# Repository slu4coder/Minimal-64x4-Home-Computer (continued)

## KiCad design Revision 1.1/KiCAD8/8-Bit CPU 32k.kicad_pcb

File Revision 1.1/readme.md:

# Revision 1.1 (Original Release)

The folder 'KiCAD' contains KiCAD 6 schematics. The folder 'KiCAD8' contains the same schematics with minor cosmetic updates, converted to KiCAD8.
For the bill of materials (BOM) please refer to chapter 'Hardware' of the 'Minimal 64x4 Reference Manual'. Follow the link in the root readme.md of this repo.

The folder 'Support' contains the cross-platform assembler und the emulator (Win).
The folder 'Programs' contains native Minimal 64x4 code.

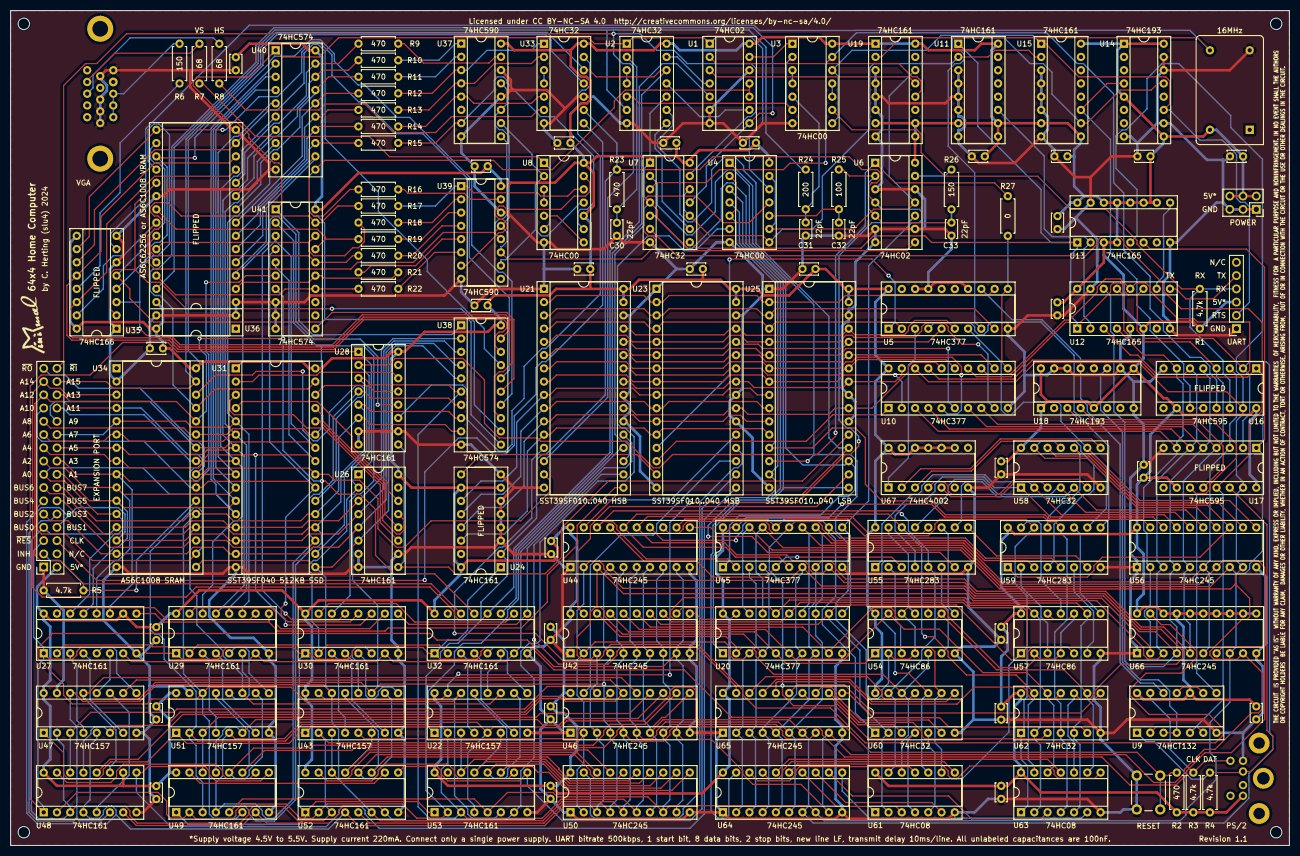
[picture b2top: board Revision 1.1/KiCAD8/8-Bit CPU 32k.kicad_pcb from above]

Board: 2 copper layers, 245.1 x 160.0 mm, 138 parts (0 on the bottom side), 267 nets.

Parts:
C1, C2, C3, C4, C5, C6, C7, C8, C9, C10, C11, C12, C13, C14, C15, C16, C17, C18, C19, C20, C21, C22, C23, C24, C25, C26, C27, C28, C29: 100nF; C_Disc_D3.4mm_W2.1mm_P2.50mm
C30, C31, C32, C33: 22pF; C_Disc_D3.4mm_W2.1mm_P2.50mm
H1, H2, H3, H4: M2; MountingHole_2.2mm_M2
J1: UART; PinSocket_1x06_P2.54mm_Vertical
J2: PS/2; FP_MINI_DIN_6_PS2
J3: EXPANSION PORT; PinSocket_2x16_P2.54mm_Vertical
J4: VGA; VGA DSUB15HD_female
J5: POWER; PinSocket_2x03_P2.54mm_Vertical
R1, R3, R4, R5: 4.7k; R_Axial_DIN0207_L6.3mm_D2.5mm_P7.62mm_Horizontal
R2, R9, R10, R11, R12, R13, R14, R15, R16, R17, R18, R19, R20, R21, R22, R23: 470; R_Axial_DIN0207_L6.3mm_D2.5mm_P7.62mm_Horizontal
R6, R26: 150; R_Axial_DIN0207_L6.3mm_D2.5mm_P7.62mm_Horizontal
R7, R8: 68; R_Axial_DIN0207_L6.3mm_D2.5mm_P7.62mm_Horizontal
R24: 200; R_Axial_DIN0207_L6.3mm_D2.5mm_P7.62mm_Horizontal
R25: 100; R_Axial_DIN0207_L6.3mm_D2.5mm_P7.62mm_Horizontal
R27: 0; R_Axial_DIN0207_L6.3mm_D2.5mm_P7.62mm_Horizontal
SW1: RESET; SW_PUSH_6mm
U1, U6: 74HC02; DIP-14_W7.62mm_Socket
U2, U7, U33, U58, U60, U62: 74HC32; DIP-14_W7.62mm_Socket
U3, U4, U8: 74HC00; DIP-14_W7.62mm_Socket
U5, U10, U20, U45: 74HC377; DIP-20_W7.62mm_Socket
U9: 74HCT132; DIP-14_W7.62mm_Socket
U11, U15, U19, U24, U26, U27, U28, U29, U30, U32, U48, U49, U52, U53: 74HC161; DIP-16_W7.62mm_Socket
U12, U13: 74HC165; DIP-16_W7.62mm_Socket
U14, U18: 74HC193; DIP-16_W7.62mm_Socket
U16, U17: 74HC595; DIP-16_W7.62mm_Socket
U21: SST39SF010..040 HSB; DIP-32_W15.24mm_Socket
U22, U43, U47, U51: 74HC157; DIP-16_W7.62mm_Socket
U23: SST39SF010..040 MSB; DIP-32_W15.24mm_Socket
U25: SST39SF010..040 LSB; DIP-32_W15.24mm_Socket
U31: SST39SF040 512KB SSD; DIP-32_W15.24mm_Socket
U34: AS6C1008 SRAM; DIP-32_W15.24mm_Socket
U35: 74HC166; DIP-16_W7.62mm_Socket
U36: AS6C62256 or AS6C1008 VRAM; DIP-32_W15.24mm_Socket
U37, U39: 74HC590; DIP-16_W7.62mm_Socket
U38, U40, U41: 74HC574; DIP-20_W7.62mm_Socket
U42, U44, U46, U50, U56, U64, U65, U66: 74HC245; DIP-20_W7.62mm_Socket
U54, U57: 74HC86; DIP-14_W7.62mm_Socket
U55, U59: 74HC283; DIP-16_W7.62mm_Socket
U61, U63: 74HC08; DIP-14_W7.62mm_Socket
U67: 74HC4002; DIP-14_W7.62mm_Socket
X1: 16MHz; Oscillator_DIP-14

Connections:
16MHz: U19.2 (CP), U35.7 (CP), X1.8 (OUT)
+5V: C1.1, C2.1, C3.1, C4.1, C5.1, C6.1, C7.1, C8.1, C9.1, C10.1, C11.1, C12.1, C13.1, C14.1, C15.1, C16.1, C17.1, C18.1, C19.1, C20.1, C21.1, C22.1, C23.1, C24.1, C25.1, C26.1, C27.1, C28.1, C29.1, J1.3, J2.4, J3.2, J5.2, J5.4, J5.6, R1.1, R2.1, R3.1, R4.1, U1.14 (VCC), U2.14 (VCC), U3.14 (VCC), U4.14 (VCC), U5.20 (VCC), U6.14 (VCC), U7.14 (VCC), U8.10, U8.14 (VCC), U9.10, U9.14 (VCC), U10.20 (VCC), U11.7 (CEP), U11.9 (~PE), U11.10 (CET), U11.16 (VCC), U12.6 (D7), U12.16 (VCC), U13.3 (D4), U13.4 (D5), U13.10 (DS), U13.11 (D0), U13.12 (D1), U13.13 (D2), U13.14 (D3), U13.16 (VCC), U14.1 (D1), U14.5 (CPU), U14.9 (D3), U14.16 (VCC), U15.7 (CEP), U15.9 (~PE), U15.16 (VCC), U16.10 (~SRCLR), U16.16 (VCC), U17.10 (~SRCLR), U17.16 (VCC), U18.1 (D1), U18.5 (CPU), U18.9 (D3), U18.16 (VCC), U19.1 (~MR), U19.7 (CEP), U19.9 (~PE), U19.10 (CET), U19.16 (VCC), U20.20 (VCC), U21.31 (~WE), U21.32 (VCC), U22.16 (VCC), U23.31 (~WE), U23.32 (VCC), U24.7 (CEP), U24.10 (CET), U24.16 (VCC), U25.31 (~WE), U25.32 (VCC), U26.16 (VCC), U27.10 (CET), U27.16 (VCC), U28.16 (VCC), U29.16 (VCC), U30.16 (VCC), U31.32 (VCC), U32.16 (VCC), U33.14 (VCC), U34.32 (VCC), U35.9 (MR), U35.16 (VCC), U36.30 (CE2), U36.32 (VCC), U37.16 (VCC), U38.20 (VCC), U39.16 (VCC), U40.20 (VCC), U41.20 (VCC), U42.20 (VCC), U43.16 (VCC), U44.20 (VCC), U45.20 (VCC), U46.20 (VCC), U47.16 (VCC), U48.10 (CET), U48.16 (VCC), U49.16 (VCC), U50.20 (VCC), U51.16 (VCC), U52.16 (VCC), U53.16 (VCC), U54.14 (VCC), U55.16 (VCC), U56.20 (VCC), U57.14 (VCC), U58.14 (VCC), U59.16 (VCC), U60.14 (VCC), U61.14 (VCC), U62.14 (VCC), U63.14 (VCC), U64.20 (VCC), U65.20 (VCC), U66.11 (B7), U66.12 (B6), U66.13 (B5), U66.14 (B4), U66.15 (B3), U66.16 (B2), U66.17 (B1), U66.18 (B0), U66.20 (VCC), U67.9, U67.10, U67.11, U67.12, U67.14 (VDD), X1.14 (Vcc)
/ALU/A0: U44.18 (B0), U45.2 (Q0), U55.5 (A1), U60.13, U61.13
/ALU/A1: U44.17 (B1), U45.5 (Q1), U55.3 (A2), U60.10, U61.10
/ALU/A2: U44.16 (B2), U45.6 (Q2), U55.14 (A3), U62.13, U63.13
/ALU/A3: U44.15 (B3), U45.9 (Q3), U55.12 (A4), U62.10, U63.10
/ALU/A4: U44.14 (B4), U45.12 (Q4), U59.5 (A1), U60.1, U61.1
/ALU/A5: U44.13 (B5), U45.15 (Q5), U59.3 (A2), U60.4, U61.4
/ALU/A6: U44.12 (B6), U45.16 (Q6), U59.14 (A3), U62.1, U63.1
/ALU/A7: U44.11 (B7), U45.19 (Q7), U59.12 (A4), U62.4, U63.4
/ALU/B0: U20.2 (Q0), U42.18 (B0), U54.5, U60.12, U61.12
/ALU/B1: U20.5 (Q1), U42.17 (B1), U54.1, U60.9, U61.9
/ALU/B2: U20.6 (Q2), U42.16 (B2), U54.13, U62.12, U63.12
/ALU/B3: U20.9 (Q3), U42.15 (B3), U54.9, U62.9, U63.9
/ALU/B4: U20.12 (Q4), U42.14 (B4), U57.5, U60.2, U61.2
/ALU/B5: U20.15 (Q5), U42.13 (B5), U57.1, U60.5, U61.5
/ALU/B6: U20.16 (Q6), U42.12 (B6), U57.13, U62.2, U63.2
/ALU/B7: U20.19 (Q7), U42.11 (B7), U57.9, U62.5, U63.5
/ALU/BUS0: J3.7, U10.3 (D0), U12.4 (D5), U16.7 (QH), U17.7 (QH), U20.3 (D0), U26.3 (D0), U31.13 (I/O0), U34.13 (I/O0), U38.2 (D0), U42.2 (A0), U43.2 (I0a), U44.2 (A0), U45.3 (D0), U46.2 (A0), U47.2 (I0a), U48.3 (D0), U50.2 (A0), U52.3 (D0), U56.2 (A0), U64.2 (A0), U65.2 (A0), U66.2 (A0)
/ALU/BUS1: J3.8, U10.4 (D1), U12.3 (D4), U16.6 (QG), U17.6 (QG), U20.4 (D1), U26.4 (D1), U31.14 (I/O1), U34.14 (I/O1), U38.3 (D1), U42.3 (A1), U43.5 (I0b), U44.3 (A1), U45.4 (D1), U46.3 (A1), U47.5 (I0b), U48.4 (D1), U50.3 (A1), U52.4 (D1), U56.3 (A1), U64.3 (A1), U65.3 (A1), U66.3 (A1)
/ALU/BUS2: J3.9, U10.7 (D2), U12.14 (D3), U16.5 (QF), U17.5 (QF), U20.7 (D2), U26.5 (D2), U31.15 (I/O2), U34.15 (I/O2), U38.4 (D2), U42.4 (A2), U43.11 (I0c), U44.4 (A2), U45.7 (D2), U46.4 (A2), U47.11 (I0c), U48.5 (D2), U50.4 (A2), U52.5 (D2), U56.4 (A2), U64.4 (A2), U65.4 (A2), U66.4 (A2)
/ALU/BUS3: J3.10, U10.8 (D3), U12.13 (D2), U16.4 (QE), U17.4 (QE), U20.8 (D3), U26.6 (D3), U31.17 (I/O3), U34.17 (I/O3), U38.5 (D3), U42.5 (A3), U43.14 (I0d), U44.5 (A3), U45.8 (D3), U46.5 (A3), U47.14 (I0d), U48.6 (D3), U50.5 (A3), U52.6 (D3), U56.5 (A3), U64.5 (A3), U65.5 (A3), U66.5 (A3)
/ALU/BUS4: J3.11, U10.13 (D4), U12.12 (D1), U16.3 (QD), U17.3 (QD), U20.13 (D4), U22.2 (I0a), U28.3 (D0), U31.18 (I/O4), U34.18 (I/O4), U38.6 (D4), U42.6 (A4), U44.6 (A4), U45.13 (D4), U46.6 (A4), U49.3 (D0), U50.6 (A4), U51.2 (I0a), U53.3 (D0), U56.6 (A4), U64.6 (A4), U65.6 (A4), U66.6 (A4)
/ALU/BUS5: J3.12, U10.14 (D5), U12.11 (D0), U16.2 (QC), U17.2 (QC), U20.14 (D5), U22.5 (I0b), U28.4 (D1), U31.19 (I/O5), U34.19 (I/O5), U38.7 (D5), U42.7 (A5), U44.7 (A5), U45.14 (D5), U46.7 (A5), U49.4 (D1), U50.7 (A5), U51.5 (I0b), U53.4 (D1), U56.7 (A5), U64.7 (A5), U65.7 (A5), U66.7 (A5)
/ALU/BUS6: J3.13, U10.17 (D6), U13.6 (D7), U16.1 (QB), U17.1 (QB), U20.17 (D6), U22.11 (I0c), U28.5 (D2), U31.20 (I/O6), U34.20 (I/O6), U38.8 (D6), U42.8 (A6), U44.8 (A6), U45.17 (D6), U46.8 (A6), U49.5 (D2), U50.8 (A6), U51.11 (I0c), U53.5 (D2), U56.8 (A6), U64.8 (A6), U65.8 (A6), U66.8 (A6)
/ALU/BUS7: J3.14, U10.18 (D7), U13.5 (D6), U16.15 (QA), U17.15 (QA), U20.18 (D7), U22.14 (I0d), U28.6 (D3), U31.21 (I/O7), U34.21 (I/O7), U38.9 (D7), U42.9 (A7), U44.9 (A7), U45.18 (D7), U46.9 (A7), U49.6 (D3), U50.9 (A7), U51.14 (I0d), U53.6 (D3), U56.9 (A7), U64.9 (A7), U65.9 (A7), U66.9 (A7)
/ALU/C_FLG: U5.4 (D1), U59.9 (C4)
/ALU/EC: U4.4, U25.15 (I/O2), U55.7 (C0)
/ALU/ES: U4.1, U25.14 (I/O1), U54.2, U54.4, U54.10, U54.12, U57.2, U57.4, U57.10, U57.12
/ALU/N_FLG: U5.7 (D2), U56.11 (B7), U58.9, U59.10 (S4)
/ALU/Z_FLG: U5.3 (D0), U67.1
/ALU/~AND: U4.3, U64.19 (CE)
/ALU/~EO: U4.2, U4.5, U25.13 (I/O0), U56.19 (CE)
/ALU/~OR: U4.6, U65.19 (CE)
/Control Logic/2MHz: U1.2, U19.12 (Q2)
/Control Logic/4MHz: U1.3, U19.13 (Q1)
/Control Logic/8MHz: U4.9, U4.13, U6.11, U19.14 (Q0)
/Control Logic/CE: U23.21 (I/O7), U48.7 (CEP), U49.7 (CEP), U52.7 (CEP), U53.7 (CEP)
/Control Logic/Flag0: U5.2 (Q0), U21.4 (A12), U23.4 (A12), U25.4 (A12)
/Control Logic/Flag1: U5.5 (Q1), U21.28 (A13), U23.28 (A13), U25.28 (A13)
/Control Logic/Flag2: U5.6 (Q2), U21.29 (A14), U23.29 (A14), U25.29 (A14)
/Control Logic/Flag3: U5.9 (Q3), U21.3 (A15), U23.3 (A15), U25.3 (A15)
/Control Logic/Flag4: U5.12 (Q4), U21.2 (A16), U23.2 (A16), U25.2 (A16)
/Control Logic/Inst0: U10.2 (Q0), U21.8 (A4), U23.8 (A4), U25.8 (A4)
/Control Logic/Inst1: U10.5 (Q1), U21.7 (A5), U23.7 (A5), U25.7 (A5)
/Control Logic/Inst2: U10.6 (Q2), U21.6 (A6), U23.6 (A6), U25.6 (A6)
/Control Logic/Inst3: U10.9 (Q3), U21.5 (A7), U23.5 (A7), U25.5 (A7)
/Control Logic/Inst4: U10.12 (Q4), U21.27 (A8), U23.27 (A8), U25.27 (A8)
/Control Logic/Inst5: U10.15 (Q5), U21.26 (A9), U23.26 (A9), U25.26 (A9)
/Control Logic/Inst6: U10.16 (Q6), U21.23 (A10), U23.23 (A10), U25.23 (A10)
/Control Logic/Inst7: U10.19 (Q7), U21.25 (A11), U23.25 (A11), U25.25 (A11)
/Control Logic/MC: U21.20 (I/O6), U22.1 (S), U43.1 (S), U47.1 (S), U51.1 (S)
/Control Logic/ME: U21.21 (I/O7), U27.7 (CEP), U29.7 (CEP), U30.7 (CEP), U32.7 (CEP)
/Control Logic/MZ: U6.10, U22.15 (E), U43.15 (E)
/Control Logic/Step0: U21.12 (A0), U23.12 (A0), U24.14 (Q0), U25.12 (A0)
/Control Logic/Step1: U21.11 (A1), U23.11 (A1), U24.13 (Q1), U25.11 (A1)
/Control Logic/Step2: U21.10 (A2), U23.10 (A2), U24.12 (Q2), U25.10 (A2)
/Control Logic/Step3: U21.9 (A3), U23.9 (A3), U24.11 (Q3), U25.9 (A3)
/Control Logic/VREG_CP: U1.10, U1.11, U38.11 (Cp), U40.11 (Cp), U41.11 (Cp)
/Control Logic/~AI: U7.2, U25.19 (I/O5), U45.1 (EN)
/Control Logic/~AO: U2.9, U25.20 (I/O6), U44.19 (CE)
/Control Logic/~BI: U7.5, U20.1 (EN), U25.17 (I/O3)
/Control Logic/~BO: U25.18 (I/O4), U42.19 (CE)
/Control Logic/~CIH: U23.18 (I/O4), U52.9 (~PE), U53.9 (~PE)
/Control Logic/~CIL: U23.17 (I/O3), U48.9 (~PE), U49.9 (~PE)
/Control Logic/~COH: U23.20 (I/O6), U50.19 (CE)
/Control Logic/~COL: U23.19 (I/O5), U46.19 (CE)
/Control Logic/~FF: U21.13 (I/O0), U66.19 (CE)
/Control Logic/~FI: U5.1 (EN), U23.13 (I/O0)
/Control Logic/~IC: U23.15 (I/O2), U24.9 (~PE)
/Control Logic/~II: U10.1 (EN), U23.14 (I/O1)
/Control Logic/~KO: U7.6, U9.5, U17.13 (~OE)
/Control Logic/~MIH: U21.18 (I/O4), U30.9 (~PE), U32.9 (~PE)
/Control Logic/~MIL: U21.17 (I/O3), U27.9 (~PE), U29.9 (~PE)
/Control Logic/~MZ: U2.10, U6.8, U7.1, U7.4, U21.19 (I/O5)
/Control Logic/~NI: U25.21 (I/O7), U26.9 (~PE), U28.9 (~PE)
/Control Logic/~PS2_DR: U5.13 (D4), U9.12, U18.13 (~TCD)
/Control Logic/~RI_PLS: U1.8, U7.11, U31.31 (~WE), U34.29 (~WE)
/Control Logic/~RI: J3.32, U7.13, U21.14 (I/O1)
/Control Logic/~RO: J3.31, U21.15 (I/O2), U31.24 (~OE), U34.24 (~OE)
/Control Logic/~TI_PLS: U7.8, U11.1 (~MR), U12.1 (~PL), U13.1 (~PL)
/Control Logic/~TO: U3.13, U7.3, U16.13 (~OE)
/Control Logic/~UART_DR: U5.8 (D3), U14.13 (~TCD), U15.10 (CET)
/Control Logic/~VREG_OE: U1.1, U2.1, U4.12, U38.1 (OE), U40.1 (OE), U41.1 (OE)
/Control Logic/~V_NEXT: U4.11, U35.15 (PE), U36.24 (~OE), U37.11 (CPC), U37.13 (CPR), U39.11 (CPC), U39.13 (CPR)
/Control Logic/~V_RI_PLS: R24.1, U2.6, U36.29 (~WE)
/Memory and MAR/BANK0: U26.14 (Q0), U31.4 (A12)
/Memory and MAR/BANK1: U26.13 (Q1), U31.28 (A13)
/Memory and MAR/BANK2: U26.12 (Q2), U31.29 (A14)
/Memory and MAR/BANK3: U26.11 (Q3), U31.3 (A15)
/Memory and MAR/BANK4: U28.14 (Q0), U31.2 (A16)
/Memory and MAR/BANK5: U28.13 (Q1), U31.30 (A17)
/Memory and MAR/BANK6: U28.12 (Q2), U31.1 (A18)
/Memory and MAR/BANK7: U28.11 (Q3), U33.13
/Memory and MAR/INH: J3.3, R5.2, U34.22 (~CE)
/PS2 Receiver/PS2_CLK: J2.5, R3.2, U9.13
/PS2 Receiver/PS2_DAT: J2.1, R4.2, U9.1, U17.14 (SER)
/UART/UART_RTS: J1.2, U3.8, U3.12, U14.11 (~PL), U15.1 (~MR)
/UART/UART_RX: J1.4, R1.2, U3.9, U16.14 (SER)
/UART/UART_TX: J1.5, U12.9 (Q7)
/VGA/B0: U35.14 (D7), U36.13 (I/O0), U38.19 (Q0)
/VGA/B1: U35.12 (D6), U36.14 (I/O1), U38.18 (Q1)
/VGA/B2: U35.11 (D5), U36.15 (I/O2), U38.17 (Q2)
/VGA/B3: U35.10 (D4), U36.17 (I/O3), U38.16 (Q3)
/VGA/B4: U35.5 (D3), U36.18 (I/O4), U38.15 (Q4)
/VGA/B5: U35.4 (D2), U36.19 (I/O5), U38.14 (Q5)
/VGA/B6: U35.3 (D1), U36.20 (I/O6), U38.13 (Q6)
/VGA/B7: U35.2 (D0), U36.21 (I/O7), U38.12 (Q7)
/VGA/H1: R9.2, U37.15 (Q0)
/VGA/H2: R10.2, U37.1 (Q1)
/VGA/H4: R11.2, U37.2 (Q2)
/VGA/H8: R12.2, U33.1, U37.3 (Q3)
/VGA/H16: R13.2, U33.2, U37.4 (Q4)
/VGA/H32: R14.2, U33.5, U37.5 (Q5)
/VGA/V1: R15.2, U8.9, U37.7 (Q7)
/VGA/V2: R16.2, U39.15 (Q0)
/VGA/V4: R17.1, U8.12, U39.1 (Q1)
/VGA/V8: R18.1, U39.2 (Q2)
/VGA/V16: R19.1, U39.3 (Q3)
/VGA/V32: R20.1, U39.4 (Q4)
/VGA/V64: R21.2, U39.5 (Q5)
/VGA/V128: R22.1, U39.6 (Q6)
/VGA/V256: U8.13, U39.7 (Q7)
/VGA/V_A0: R9.1, U36.12 (A0), U40.19 (Q0)
/VGA/V_A1: R10.1, U36.11 (A1), U40.18 (Q1)
/VGA/V_A2: R11.1, U36.10 (A2), U40.17 (Q2)
/VGA/V_A3: R12.1, U36.9 (A3), U40.16 (Q3)
/VGA/V_A4: R13.1, U36.8 (A4), U40.15 (Q4)
/VGA/V_A5: R14.1, U36.7 (A5), U40.14 (Q5)
/VGA/V_A6: R15.1, U36.6 (A6), U40.13 (Q6)
/VGA/V_A7: R16.1, U36.5 (A7), U40.12 (Q7)
/VGA/V_A8: R17.2, U36.27 (A8), U41.19 (Q0)
/VGA/V_A9: R18.2, U36.26 (A9), U41.18 (Q1)
/VGA/V_A10: R19.2, U36.23 (A10), U41.17 (Q2)
/VGA/V_A11: R20.2, U36.25 (A11), U41.16 (Q3)
/VGA/V_A12: R21.1, U36.4 (A12), U41.15 (Q4)
/VGA/V_A13: R22.2, U36.28 (A13), U41.14 (Q5)
A0: J3.15, U27.14 (Q0), U31.12 (A0), U34.12 (A0), U40.2 (D0)
A1: J3.16, U27.13 (Q1), U31.11 (A1), U34.11 (A1), U40.3 (D1)
A2: J3.17, U27.12 (Q2), U31.10 (A2), U34.10 (A2), U40.4 (D2)
A3: J3.18, U27.11 (Q3), U31.9 (A3), U34.9 (A3), U40.5 (D3)
A4: J3.19, U29.14 (Q0), U31.8 (A4), U34.8 (A4), U40.6 (D4)
A5: J3.20, U29.13 (Q1), U31.7 (A5), U34.7 (A5), U40.7 (D5)
A6: J3.21, U29.12 (Q2), U31.6 (A6), U34.6 (A6), U40.8 (D6)
A7: J3.22, U29.11 (Q3), U31.5 (A7), U34.5 (A7), U40.9 (D7)
A8: J3.23, U30.14 (Q0), U31.27 (A8), U34.27 (A8), U41.2 (D0)
A9: J3.24, U30.13 (Q1), U31.26 (A9), U34.26 (A9), U41.3 (D1)
A10: J3.25, U30.12 (Q2), U31.23 (A10), U34.23 (A10), U41.4 (D2)
A11: J3.26, U30.11 (Q3), U31.25 (A11), U34.25 (A11), U41.5 (D3)
A12: J3.27, U32.14 (Q0), U34.4 (A12), U41.6 (D4)
A13: J3.28, U32.13 (Q1), U34.28 (A13), U41.7 (D5)
A14: J3.29, U1.5, U32.12 (Q2), U34.3 (A14)
A15: J3.30, U2.12, U32.11 (Q3), U33.12, U34.31 (A15)
CLK_MAR: R27.2, U6.1, U26.2 (CP), U27.2 (CP), U28.2 (CP), U29.2 (CP), U30.2 (CP), U32.2 (CP)
CLK_PC: R23.1, U6.4, U20.11 (CP), U24.2 (CP), U33.9, U45.11 (CP), U48.2 (CP), U49.2 (CP), U52.2 (CP), U53.2 (CP)
GND: C1.2, C2.2, C3.2, C4.2, C5.2, C6.2, C7.2, C8.2, C9.2, C10.2, C11.2, C12.2, C13.2, C14.2, C15.2, C16.2, C17.2, C18.2, C19.2, C20.2, C21.2, C22.2, C23.2, C24.2, C25.2, C26.2, C27.2, C28.2, C29.2, C30.2, C31.2, C32.2, C33.2, J1.1, J2.3, J3.1, J4.5, J4.6, J4.7, J4.8, J4.10, J5.1, J5.3, J5.5, R5.1, SW1.2, U1.6, U1.7 (GND), U1.12, U2.7 (GND), U3.7 (GND), U4.7 (GND), U5.10 (GND), U5.14 (D5), U5.17 (D6), U5.18 (D7), U6.3, U6.6, U6.7 (GND), U6.9, U6.12, U7.7 (GND), U8.7 (GND), U9.7 (GND), U10.10 (GND), U11.3 (D0), U11.4 (D1), U11.5 (D2), U11.6 (D3), U11.8 (GND), U12.5 (D6), U12.8 (GND), U12.15 (~CE), U13.8 (GND), U13.15 (~CE), U14.8 (GND), U14.10 (D2), U14.14 (MR), U14.15 (D0), U15.3 (D0), U15.4 (D1), U15.5 (D2), U15.6 (D3), U15.8 (GND), U16.8 (GND), U17.8 (GND), U18.8 (GND), U18.10 (D2), U18.14 (MR), U18.15 (D0), U19.3 (D0), U19.4 (D1), U19.5 (D2), U19.6 (D3), U19.8 (GND), U20.10 (GND), U21.1 (A18), U21.16 (GND), U21.22 (~CE), U21.24 (~OE), U21.30 (A17), U22.8 (GND), U23.1 (A18), U23.16 (GND), U23.22 (~CE), U23.24 (~OE), U23.30 (A17), U24.3 (D0), U24.4 (D1), U24.5 (D2), U24.6 (D3), U24.8 (GND), U25.1 (A18), U25.16 (GND), U25.22 (~CE), U25.24 (~OE), U25.30 (A17), U26.7 (CEP), U26.8 (GND), U26.10 (CET), U27.8 (GND), U28.7 (CEP), U28.8 (GND), U28.10 (CET), U29.8 (GND), U30.8 (GND), U31.16 (GND), U32.8 (GND), U33.7 (GND), U33.10, U34.2 (A16), U34.16 (GND), U35.1 (Ds), U35.6 (CE), U35.8 (GND), U36.2 (A16), U36.3 (A14), U36.16 (GND), U36.22 (~CE), U36.31 (A15), U37.8 (GND), U37.12 (~CE), U37.14 (~OE), U38.10 (GND), U39.8 (GND), U39.14 (~OE), U40.10 (GND), U41.8 (D6), U41.9 (D7), U41.10 (GND), U42.1 (A->B), U42.10 (GND), U43.8 (GND), U44.1 (A->B), U44.10 (GND), U45.10 (GND), U46.1 (A->B), U46.10 (GND), U47.8 (GND), U47.15 (E), U48.8 (GND), U49.8 (GND), U50.1 (A->B), U50.10 (GND), U51.8 (GND), U51.15 (E), U52.8 (GND), U53.8 (GND), U54.7 (GND), U55.8 (GND), U56.1 (A->B), U56.10 (GND), U57.7 (GND), U58.7 (GND), U59.8 (GND), U60.7 (GND), U61.7 (GND), U62.7 (GND), U63.7 (GND), U64.1 (A->B), U64.10 (GND), U65.1 (A->B), U65.10 (GND), U66.1 (A->B), U66.10 (GND), U67.7 (VSS), X1.7 (GND)
unnamed: C30.1, R23.2, U2.2
unnamed: C31.1, R24.2, U3.5
unnamed: C32.1, R25.2, U4.10
unnamed: C33.1, R25.1, R26.2, U6.2, U6.5
unnamed: J3.6, U33.8
unnamed: J4.1, J4.2, J4.3, R6.2
unnamed: J4.13, R8.1
unnamed: J4.14, R7.1
unnamed: R7.2, U8.1, U8.6
unnamed: R8.2, U33.6
unnamed: R26.1, U6.13
unnamed: U1.4, U2.13
unnamed: U1.9, U2.11
unnamed: U1.13, U3.1
unnamed: U2.3, U2.4
unnamed: U2.5, U3.2, U3.6
unnamed: U2.8, U7.9
unnamed: U3.3, U3.4
unnamed: U3.10, U3.11
unnamed: U8.3, U8.4
unnamed: U8.5, U8.8
unnamed: U9.2, U9.6
unnamed: U9.9, U9.11
unnamed: R27.1, U5.11 (CP), U10.11 (CP)
unnamed: U11.11 (Q3), U12.2 (CP), U13.2 (CP)
unnamed: U12.10 (DS), U13.9 (Q7)
unnamed: U14.4 (CPD), U15.11 (Q3), U16.11 (SRCLK), U16.12 (RCLK)
unnamed: U17.12 (RCLK), U18.3 (Q0)
unnamed: U9.8, U17.11 (SRCLK), U18.4 (CPD)
unnamed: U9.3, U9.4, U18.11 (~PL)
unnamed: U22.4 (Za), U32.3 (D0)
unnamed: U22.7 (Zb), U32.4 (D1)
unnamed: U22.9 (Zc), U32.5 (D2)
unnamed: U22.12 (Zd), U32.6 (D3)
unnamed: U27.3 (D0), U47.4 (Za)
unnamed: U27.4 (D1), U47.7 (Zb)
unnamed: U27.5 (D2), U47.9 (Zc)
unnamed: U27.6 (D3), U47.12 (Zd)
unnamed: U27.15 (TC), U29.10 (CET)
unnamed: U29.3 (D0), U51.4 (Za)
unnamed: U29.4 (D1), U51.7 (Zb)
unnamed: U29.5 (D2), U51.9 (Zc)
unnamed: U29.6 (D3), U51.12 (Zd)
unnamed: U29.15 (TC), U30.10 (CET)
unnamed: U30.3 (D0), U43.4 (Za)
unnamed: U30.4 (D1), U43.7 (Zb)
unnamed: U30.5 (D2), U43.9 (Zc)
unnamed: U30.6 (D3), U43.12 (Zd)
unnamed: U30.15 (TC), U32.10 (CET)
unnamed: U31.22 (~CE), U33.11, U34.30 (CE2)
unnamed: U33.3, U33.4
unnamed: R6.1, U35.13 (Q7)
unnamed: U8.2, U8.11, U37.10 (~MRC), U39.10 (~MRC)
unnamed: U37.9 (~RCO), U39.12 (~CE)
unnamed: U48.15 (TC), U49.10 (CET)
unnamed: U49.15 (TC), U52.10 (CET)
unnamed: U52.15 (TC), U53.10 (CET)
unnamed: U54.6, U55.6 (B1)
unnamed: U54.3, U55.2 (B2)
unnamed: U54.11, U55.15 (B3)
unnamed: U54.8, U55.11 (B4)
unnamed: U55.9 (C4), U59.7 (C0)
unnamed: U55.4 (S1), U56.18 (B0), U58.1
unnamed: U55.1 (S2), U56.17 (B1), U58.2
unnamed: U55.13 (S3), U56.16 (B2), U58.4
unnamed: U55.10 (S4), U56.15 (B3), U58.5
unnamed: U56.14 (B4), U58.13, U59.4 (S1)
unnamed: U56.13 (B5), U58.12, U59.1 (S2)
unnamed: U56.12 (B6), U58.10, U59.13 (S3)
unnamed: U58.3, U67.5
unnamed: U58.6, U67.4
unnamed: U58.8, U67.2
unnamed: U58.11, U67.3
unnamed: U57.6, U59.6 (B1)
unnamed: U57.3, U59.2 (B2)
unnamed: U57.11, U59.15 (B3)
unnamed: U57.8, U59.11 (B4)
unnamed: U61.11, U64.18 (B0)
unnamed: U61.8, U64.17 (B1)
unnamed: U63.11, U64.16 (B2)
unnamed: U63.8, U64.15 (B3)
unnamed: U61.3, U64.14 (B4)
unnamed: U61.6, U64.13 (B5)
unnamed: U63.3, U64.12 (B6)
unnamed: U63.6, U64.11 (B7)
unnamed: U60.11, U65.18 (B0)
unnamed: U60.8, U65.17 (B1)
unnamed: U62.11, U65.16 (B2)
unnamed: U62.8, U65.15 (B3)
unnamed: U60.3, U65.14 (B4)
unnamed: U60.6, U65.13 (B5)
unnamed: U62.3, U65.12 (B6)
unnamed: U62.6, U65.11 (B7)
PC0: U46.18 (B0), U47.3 (I1a), U48.14 (Q0)
PC1: U46.17 (B1), U47.6 (I1b), U48.13 (Q1)
PC2: U46.16 (B2), U47.10 (I1c), U48.12 (Q2)
PC3: U46.15 (B3), U47.13 (I1d), U48.11 (Q3)
PC4: U46.14 (B4), U49.14 (Q0), U51.3 (I1a)
PC5: U46.13 (B5), U49.13 (Q1), U51.6 (I1b)
PC6: U46.12 (B6), U49.12 (Q2), U51.10 (I1c)
PC7: U46.11 (B7), U49.11 (Q3), U51.13 (I1d)
PC8: U43.3 (I1a), U50.18 (B0), U52.14 (Q0)
PC9: U43.6 (I1b), U50.17 (B1), U52.13 (Q1)
PC10: U43.10 (I1c), U50.16 (B2), U52.12 (Q2)
PC11: U43.13 (I1d), U50.15 (B3), U52.11 (Q3)
PC12: U22.3 (I1a), U50.14 (B4), U53.14 (Q0)
PC13: U22.6 (I1b), U50.13 (B5), U53.13 (Q1)
PC14: U22.10 (I1c), U50.12 (B6), U53.12 (Q2)
PC15: U22.13 (I1d), U50.11 (B7), U53.11 (Q3)
~CLK_PLS: U4.8, U7.10, U7.12, U11.2 (CP), U15.2 (CP)
~RESET: J3.5, R2.2, SW1.1, U24.1 (~MR), U26.1 (~MR), U27.1 (~MR), U28.1 (~MR), U29.1 (~MR), U30.1 (~MR), U32.1 (~MR), U48.1 (~MR), U49.1 (~MR), U52.1 (~MR), U53.1 (~MR)

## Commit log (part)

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2024-03-29 Create DISCLAIMER
2024-03-29 Create CHANGE LOG
2024-03-29 Release
2024-04-05 I've used KiCAD 6.
2024-04-27 Update CHANGE LOG
2024-04-27 INQ/DEQ/INL/DEL bugfix
2024-05-12 Bugfix in parsing upper-case hex numbers.
2024-05-15 Add gb keyboard layout
2024-05-16 {[ ;: key issue fixed
2024-05-17 Added command line support (see manual)
2024-05-17 Added support for 'autostart' (see manual)
2024-08-06 Update blocks.min
    1. i documented the shape/minos format
    2. i updated the comments on the shapes to use Z/S/I/T/J/L/O, just like https://en.wikipedia.org/wiki/Tetromino#Fixed_tetrominoes
    3. i added support for up/down/left/right arrow keys in addition to WASD. i tested this on the emulator using my US keyboard hack from #24
2024-08-09 added clear cmd and fixed comments
2024-10-10 Minor cosmetic update
2024-10-10 Cosmetic updates
2024-11-21 asm: clean up warnings, add macos compile instructions
2025-01-11 Fixing broken Ctrl+T command
2025-02-06 Fixed bug in 'format' command
2025-07-13 Restructuring
2025-07-13 Coming soon!
2025-07-13 Minimal 64x4 Redux coming soon!
2025-07-13 Redux release coming soon!
2025-07-18 Added static library support
2026-01-13 Adding a Linux version
2026-01-13 Fix formatting in emulator readme.md
2026-06-22 Correct number of 74HCxx logic ICs in README
2026-06-22 Revise README for Minimal 64x4 Home Computer 1.4
    Updated README to reflect version 1.4 release.
